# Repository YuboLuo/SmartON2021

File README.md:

# SmartOn: Just-in-Time Active Event Detection on Energy Harvesting Systems
This repository holds the relevant project files for SmartON, an energy harvesting system that performs active event detection by using reinforcement learning.

## TI_CCS
This folder includes files for CCS project. You can create a new empty project in CCS and then copy those files to the project. It should work. This project uses driverlib library so when you create a new empty project in CCS, be sure to choose "MSP430 DriverLib -> Empty Project with DriverLib Source" under the "Project templates and examples". The target board is MSP430Fr5994. This project was developed in CCS Version: 9.1.0.00010 

## Hardware
This folder includes files for designing the PCB board and library files for some components. This project was developed with Eagle. 

## Simulation
This folder includes files for the software simulation.

## Experiments
All experiment-related results, e.g. raw sensor data.

## Reference 
Please cite this paper in the following format for Latex. 

@INPROCEEDINGS {smarton,
author = {Y. Luo and S. Nirjon},
booktitle = {2021 17th International Conference on Distributed Computing in Sensor Systems (DCOSS)},
title = {SmartON: Just-in-Time Active Event Detection on Energy Harvesting Systems},
year = {2021},
volume = {},
issn = {},
pages = {35-44},
keywords = {event detection;power system management;capacitance;energy efficiency;hardware;software;sensor systems},
doi = {10.1109/DCOSS52077.2021.00018},
url = {https://doi.ieeecomputersociety.org/10.1109/DCOSS52077.2021.00018},
publisher = {IEEE Computer Society},
address = {Los Alamitos, CA, USA},
month = {jul}
}

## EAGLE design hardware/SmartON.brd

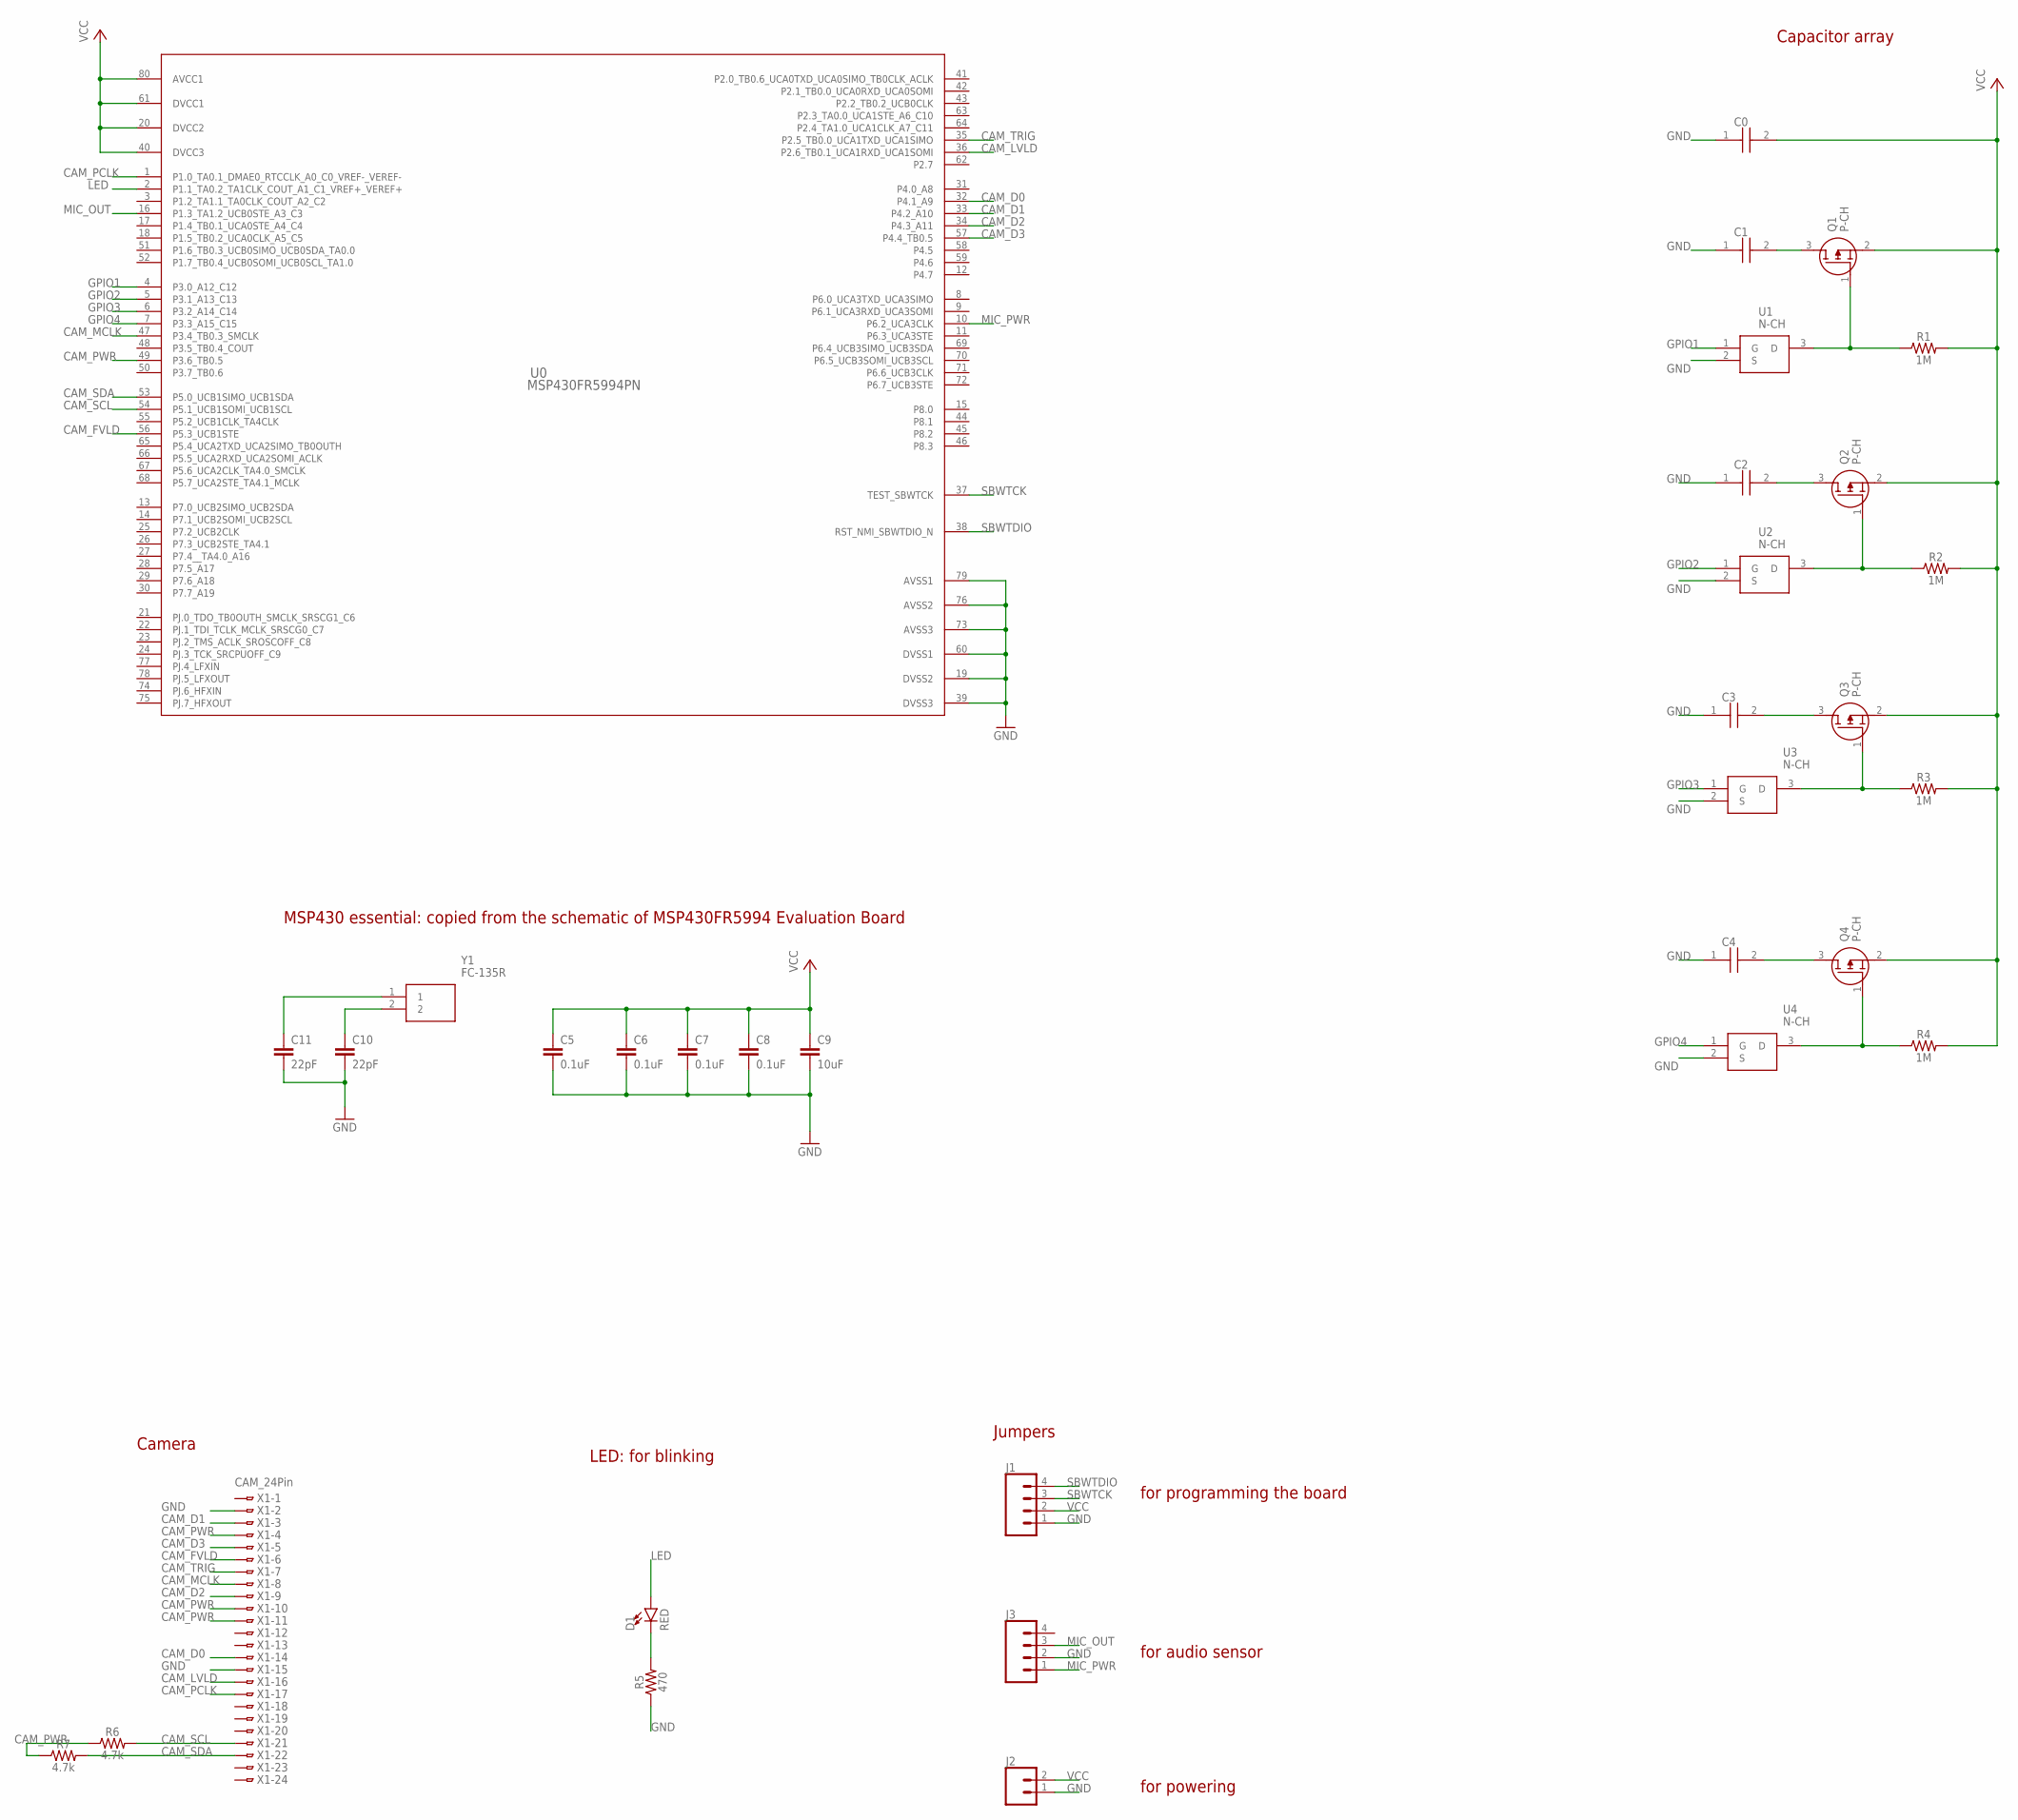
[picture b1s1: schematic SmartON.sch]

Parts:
C0, C1, C2, C3, C4: DBN-5R5D224T; CAPPRD500W130D1350H800
C5, C6, C7, C8: 0.1uF; 0603
C9: 10uF; 0603
C10, C11: 22pF; 0603
D1: RED; LED-0603
J1, J3: CONN_04LOCK; 1X04_LOCK
J2: CONN_02; 1X02
Q1, Q2, Q3, Q4: P-CH; SOT95P237X112-3N
R1, R2, R3, R4: 1M; 0603
R5: 470; 0603
R6, R7: 4.7k; 0603
U0: MSP430FR5994PN; PN0080A_N
U1, U2, U3, U4: N-CH; SOT95P240X110-3N
X1: CAM_24Pin; FH12-24S-0.5SH
Y1: FC-135R; FC135327680KAAG0

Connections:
CAM_D0: U0.32 (P4.1_A9), X1.14
CAM_D1: U0.33 (P4.2_A10), X1.3
CAM_D2: U0.34 (P4.3_A11), X1.9
CAM_D3: U0.57 (P4.4_TB0.5), X1.5
CAM_FVLD: U0.56 (P5.3_UCB1STE), X1.6
CAM_LVLD: U0.36 (P2.6_TB0.1_UCA1RXD_UCA1SOMI), X1.16
CAM_MCLK: U0.47 (P3.4_TB0.3_SMCLK), X1.8
CAM_PCLK: U0.1 (P1.0_TA0.1_DMAE0_RTCCLK_A0_C0_VREF-_VER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), X1.17
CAM_PWR: R6.1, R7.1, U0.49 (P3.6_TB0.5), X1.4, X1.10, X1.11
CAM_SCL: R6.2, U0.54 (P5.1_UCB1SOMI_UCB1SCL), X1.21
CAM_SDA: R7.2, U0.53 (P5.0_UCB1SIMO_UCB1SDA), X1.22
CAM_TRIG: U0.35 (P2.5_TB0.0_UCA1TXD_UCA1SIMO), X1.7
GND: C0.1 (+), C1.1 (+), C2.1 (+), C3.1 (+), C4.1 (+), C5.2, C6.2, C7.2, C8.2, C9.2, C10.2, C11.2, J1.1, J2.1, J3.2, R5.1, U0.19 (DVSS2), U0.39 (DVSS3), U0.60 (DVSS1), U0.73 (AVSS3), U0.76 (AVSS2), U0.79 (AVSS1), U1.2 (S), U2.2 (S), U3.2 (S), U4.2 (S), X1.2, X1.15
GPIO1: U0.4 (P3.0_A12_C12), U1.1 (G)
GPIO2: U0.5 (P3.1_A13_C13), U2.1 (G)
GPIO3: U0.6 (P3.2_A14_C14), U3.1 (G)
GPIO4: U0.7 (P3.3_A15_C15), U4.1 (G)
LED: D1.A, U0.2 (P1.1_TA0.2_TA1CLK_COUT_A1_C1_VREF+_VERE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)
MIC_OUT: J3.3, U0.16 (P1.3_TA1.2_UCB0STE_A3_C3)
MIC_PWR: J3.1, U0.10 (P6.2_UCA3CLK)
unnamed: C10.1, Y1.2
unnamed: C11.1, Y1.1
unnamed: Q1.1 (G), R1.1, U1.3 (D)
unnamed: C1.2 (-), Q1.3 (D)
unnamed: C2.2 (-), Q2.3 (D)
unnamed: C3.2 (-), Q3.3 (D)
unnamed: Q2.1 (G), R2.1, U2.3 (D)
unnamed: Q3.1 (G), R3.1, U3.3 (D)
unnamed: C4.2 (-), Q4.3 (D)
unnamed: Q4.1 (G), R4.1, U4.3 (D)
unnamed: D1.C, R5.2
SBWTCK: J1.3, U0.37 (TEST_SBWTCK)
SBWTDIO: J1.4, U0.38 (RST_NMI_SBWTDIO_N)
VCC: C0.2 (-), C5.1, C6.1, C7.1, C8.1, C9.1, J1.2, J2.2, Q1.2 (S), Q2.2 (S), Q3.2 (S), Q4.2 (S), R1.2, R2.2, R3.2, R4.2, U0.20 (DVCC2), U0.40 (DVCC3), U0.61 (DVCC1), U0.80 (AVCC1)

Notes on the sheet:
MSP430 essential: copied from the schematic of MSP430FR5994 Evaluation Board
Camera
LED: for blinking
Jumpers
for programming the board
for audio sensor
for powering
Capacitor array

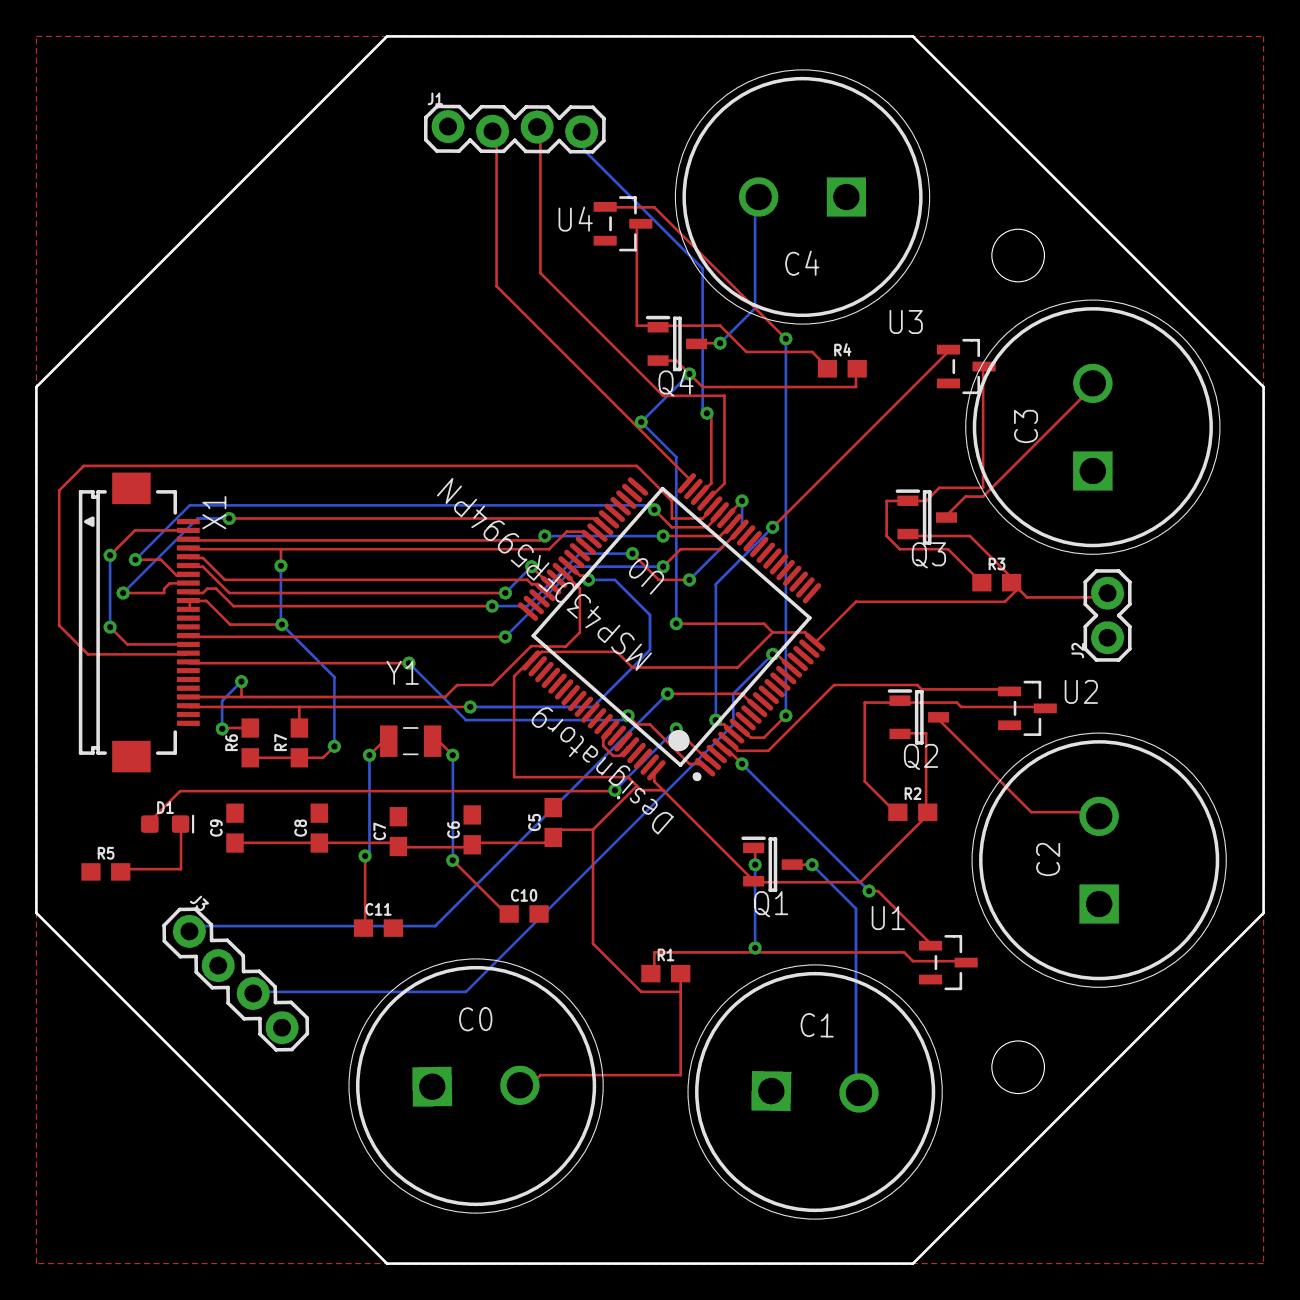
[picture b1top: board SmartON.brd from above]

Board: 2 copper layers, 70.0 x 70.0 mm, 34 parts (0 on the bottom side), 34 nets.

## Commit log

2021-05-27 initial
2021-05-30 update CCS
2021-05-30 added README for CCS
2021-09-24 add experiment related data
2021-09-24 Update README.md
    update readme
2021-09-24 add analog history
2021-12-03 Update README.md
    update reference format

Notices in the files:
parts and their libraries:
SparkFun-Capacitors: Licensing: Creative Commons ShareAlike 4.0 International - https://creativecommons.org/licenses/by-sa/4.0
